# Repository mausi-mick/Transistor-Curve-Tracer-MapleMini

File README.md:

# Transistor-Curve-Tracer-MapleMini

This project based on the super project "Transistor Curve Tracer" from Peter Balch :
https://www.instructables.com/id/Transistor-Curve-Tracer/  

I ported the software from the 8-bit Arduino platform ( hardware: Arduino Pro Mini ) to 32 bit STM32duino (hw: MapleMini).

For me was the MapleMini the best choice: cheap, quick, enough program-space, more accessible port-pins as the Arduino Uno/Nano/... and more flexibility and accuracy :

more than 5 ADC's with 12-bit resolution, 2 SPI's/, more than 2 ISR-Pins (for the encoders) and USB-socket for programming and supply. 
Also the 3.3 V port-voltage was favourable for connections to the ILI9341-spi-tft-display/touch.

For more information about MapleMini look here: https://www.stm32duino.com/
or about this project:  https://www.stm32duino.com/viewtopic.php?t=4269

Therefore I had the possibility to integrate other features:

- integration of two rotary encoders (on isr) for a more comfortable changing of the parameters, a dual DAC (MCP4822) with the same 12-bit resolution as the ADC's on the MapleMini.
- possibility to save the parameters in the internal EEPROM
- possibility compare similar or complementary devices on the same screen
- changing x-scale for diodes/zeners (0,1,2,3,4,6,12,24V) (0: starts with 24V and search the optimal scale)
- changing y-sacle for diodes from 0...10mA  to 0...50mA
- changing y-scale for MosFETs/jFETs automatic depending on max. IDss from 50mA to 10mA or 50mA to 100mA
- changing x-scale for n-jFETs from 12V (default), 6V, 4V, 3V, 2V.

The schematic of the tracer is different from Peters version:

I use switches to connect the Emitter/Source/Cathode respectively Collector/Drain/Anode to +/- supply-voltage only while measuring - most time the DUT is only with the base connected, Emtter / Collector are isolated.
At first I tested it with a dual toggle switch, than with mechanical relais, than I changed to  PhotoMosRelais because of less space on the board and less supply-current( 40ma/5V -> 2-5mA/3.3V). So the MapleMini-ports can drive the PhotoMosRelais direct.

As amplifier to drive the Emitter/Source ... Collector/Drain I made another design.
Peter used a LM358 standard dual amplifier with emitter-followers, but I think it was difficult to make it stable and there was a big drop on the positive rail.
Therefore I searched and tested some other amplfiers with drive capacibility of more than 50mA, among others NE5532 , L2272 and TCA0372.
The TCA0372 was the best in relation to stability and to low drop on the supply (r-to-r) at 50mA.
I use only one amplifier of the TCA0372 with gain = +3 (default).
The output of the TCA0372 can manage more than 100mA, the negative supply-voltage I put down to about -3V, because the TCA0372 is not a real rail-to-rail-amplifier at this currents. The negative supply near -3V is generated with a charge-pump (from+3.3V).
With the U-DAC (MCP4822) I can generate 0...12V similar the version from Peter.
As amplifier for the base-current/gate-voltage I use a LT1013 dual amplifier, because it's a R to R and can work up to max. 44V.
The TCA0372 has a normal supply-voltage from 12.6V, changing to about 26V for measuring zeners with Vz > 12V and <= 24V. Therefore I have to change the gain of the TCA0372 to +6 (V-DAC-max  (=4.095V) * 6 >=24V).
For measuring nJFETS in the ohmic-region (< Vpinch) I can switch the x-scale at the display from 12V ... to 2V.
Between 2V and 4V the gain of the TCA0372 is switched from 3 to 2, the V-DAC MCP4822 works than from 0...2.047V with step = 0,5mV.  

The LT1013 has a positive supply-voltage from around 26V, a negative supply from -12v via a LM317L and ICL7662 charge-pump.
I need the negative supply for the gates from nJFET's and depletion-mode-nMOSFET's, the positive supply > 12V for the gates from 
p-JFET's (I think it exist only one depletion-mode-pMOSFET-chip!).

The gain of the opamp's of the LT1013 can be changed from +6 to -6 with two PhotoMosRelais, or better 
over the relais I can select the opamp with the gain +6 or -6.

For npn/pnp and MosFets the I-DAC here works from 0... 2.047 V to generate 0 ... + 12 V with gain = +6 or
with gain = -6  to generate 0 ... - 12 V gatevoltage for nJFET's,
for pJFET's the I-DAC works from about 2.048 ... 4.095 V to generate gatevoltage from +12 ... +24 V for
pJFET with gain +6.

The current is limited to max 50mA . only for JFET's/MOSFET's it can go in a second step up to about 100mA.

The software is developed with the ARDUINO IDE 1.8.4, STM32duino is about one year (2017) old, but I think the newest version would work to.

You have to load  Bootloader 2.0 (20k RAM, 120k Flash) in MapleMini.

The main components are:

- ILI9341 TFT-SPI-Display 2.8" with Touch ca 6.70 €
- MapleMini                                  3.60 €
- DACMCP4822                                 3.20 € 
- AQY212 6x                                  6.00 €
- LT1013                                     1.40 €
- TCA0372                                    1.10 €
- MT3608 3x                                  2.00 €
- Rotary Encoder 2x                          2.00 €
- nMOS switch    7x                          2.00 €    
- ICL7662 (-12V) + TSP490603(-5/-3.3V)       4.00 €
-                           SUM:            32.00 €
+ resistors, capacitors, diodes, test-sockets,                                          
+ pcb's, wire, zinn, sockets, battery, chassis ...     

The hardware is nearly finsihed, the software is growing !

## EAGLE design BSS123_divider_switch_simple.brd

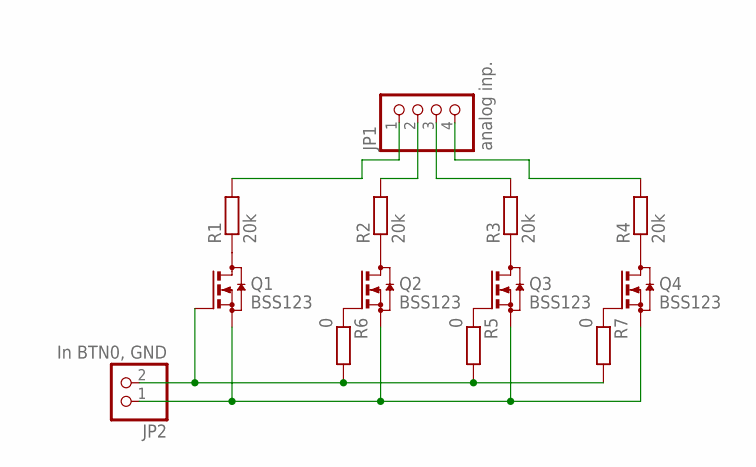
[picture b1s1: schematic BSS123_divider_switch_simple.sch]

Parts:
JP1: analog inp.; 1X04
JP2: In BTN0, GND; 1X02
Q1, Q2, Q3, Q4: BSS123; SOT23
R1, R2, R3, R4: 20k; R1206
R5, R6, R7: 0; R1206

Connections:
unnamed: Q1.3 (D), R1.1
unnamed: Q2.3 (D), R2.1
unnamed: Q3.3 (D), R3.1
unnamed: Q4.3 (D), R4.1
unnamed: Q4.1 (G), R7.1
unnamed: JP2.1, Q1.2 (S), Q2.2 (S), Q3.2 (S), Q4.2 (S)
unnamed: JP1.1, R1.2
unnamed: JP1.2, R2.2
unnamed: JP1.3, R3.2
unnamed: JP1.4, R4.2
unnamed: Q2.1 (G), R6.1
unnamed: Q3.1 (G), R5.1
unnamed: JP2.2, Q1.1 (G), R5.2, R6.2, R7.2

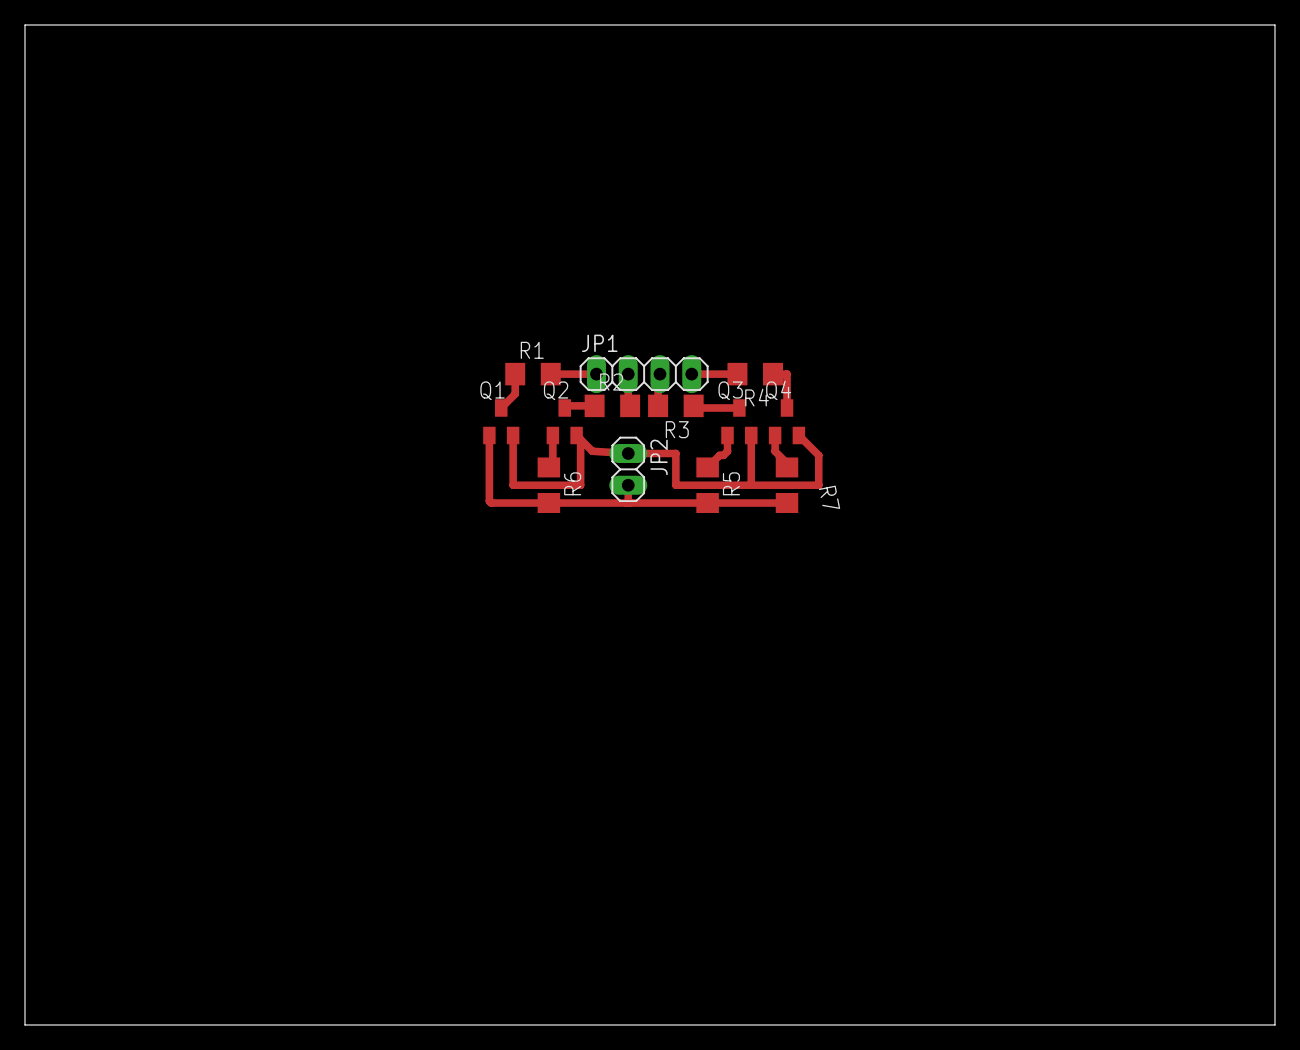
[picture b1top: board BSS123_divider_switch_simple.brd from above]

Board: 2 copper layers, 100.0 x 80.0 mm, 13 parts (0 on the bottom side), 13 nets.

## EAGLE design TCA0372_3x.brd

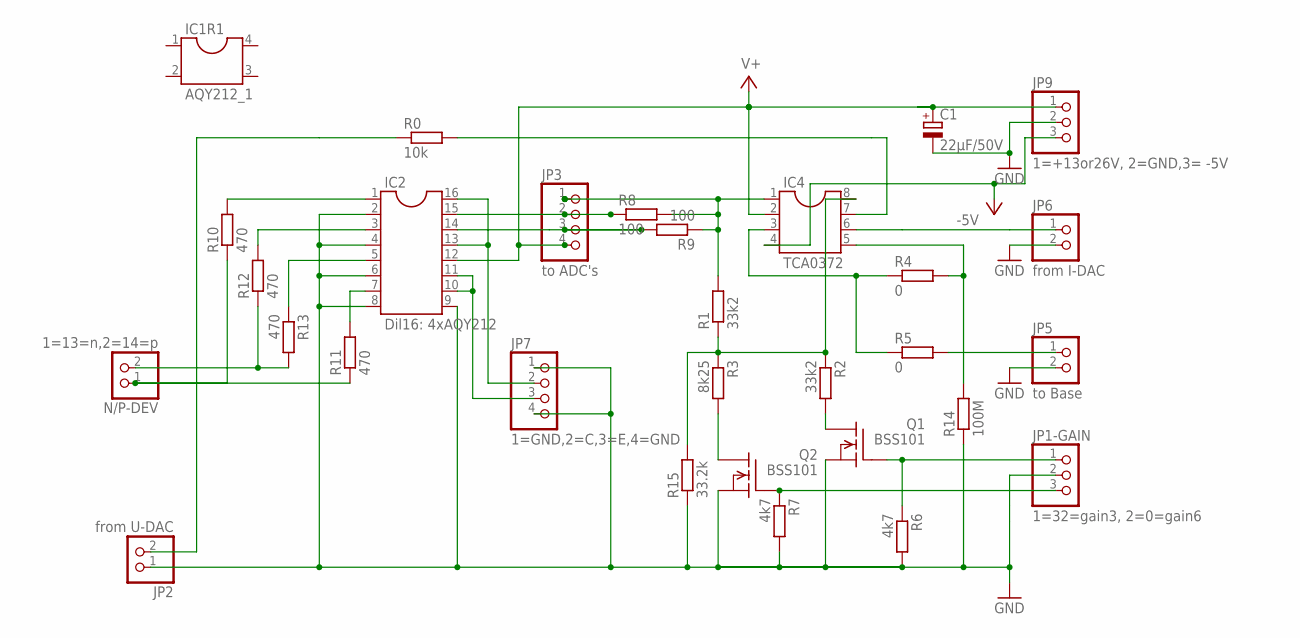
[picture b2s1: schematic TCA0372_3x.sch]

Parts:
C1: 22µF/50V; E5-10,5
IC1R1: AQY212_1; SOCKET-04
IC2: Dil16: 4xAQY212; SOCKET-16
IC4: TCA0372; SOCKET-08
JP1-GAIN: 1=32=gain3, 2=0=gain6; 1X03
JP2: from U-DAC; 1X02
JP3: to ADC's; 1X04
JP5: to Base; 1X02
JP6: from I-DAC; 1X02
JP7: 1=GND,2=C,3=E,4=GND; 1X04
JP9: 1=+13or26V, 2=GND,3= -5V; 1X03
N/P-DEV: 1=13=n,2=14=p; 1X02
Q1, Q2: BSS101; TO92
R0: 10k; 0207/7
R1, R2: 33k2; 0207/7
R3: 8k25; 0207/7
R4, R5: 0; 0207/7
R6, R7: 4k7; 0207/7
R8, R9: 100; 0207/7
R10, R11, R12, R13: 470; 0207/7
R14: 100M; 0207/7
R15: 33.2k; 0207/7

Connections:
-5V: IC4.4, JP9.3
GND: C1.-, IC2.2, IC2.4, IC2.6, IC2.8, IC2.9, JP1-GAIN.2, JP2.1, JP5.2, JP6.2, JP7.1, JP7.4, JP9.2, Q1.1 (S), Q2.1 (S), R6.2, R7.2, R14.1, R15.1
unnamed: IC4.5, R4.2, R14.2
unnamed: IC2.15, JP3.2, R8.1
unnamed: IC4.7, R0.2
unnamed: IC2.7, R11.2
unnamed: Q1.3 (D), R2.2
unnamed: Q2.3 (D), R3.2
unnamed: JP1-GAIN.1, Q1.2 (G), R6.1
unnamed: JP1-GAIN.3, Q2.2 (G), R7.1
unnamed: IC4.6, JP6.1
unnamed: IC2.3, R12.2
unnamed: IC2.13, IC2.16, JP7.2
unnamed: JP2.2, R0.1
unnamed: IC4.3, R4.1, R5.1
unnamed: IC2.5, R13.1
unnamed: N/P-DEV.2, R12.1, R13.2
unnamed: IC2.1, R10.2
unnamed: N/P-DEV.1, R10.1, R11.1
unnamed: JP5.1, R5.2
unnamed: IC4.1, JP3.1, R1.2, R8.2, R9.1
unnamed: IC4.8, R1.1, R2.1, R3.1, R15.2
unnamed: IC2.10, IC2.11, JP7.3
unnamed: IC2.14, JP3.3, R9.2
V+: C1.+, IC2.12, IC4.2, JP3.4, JP9.1

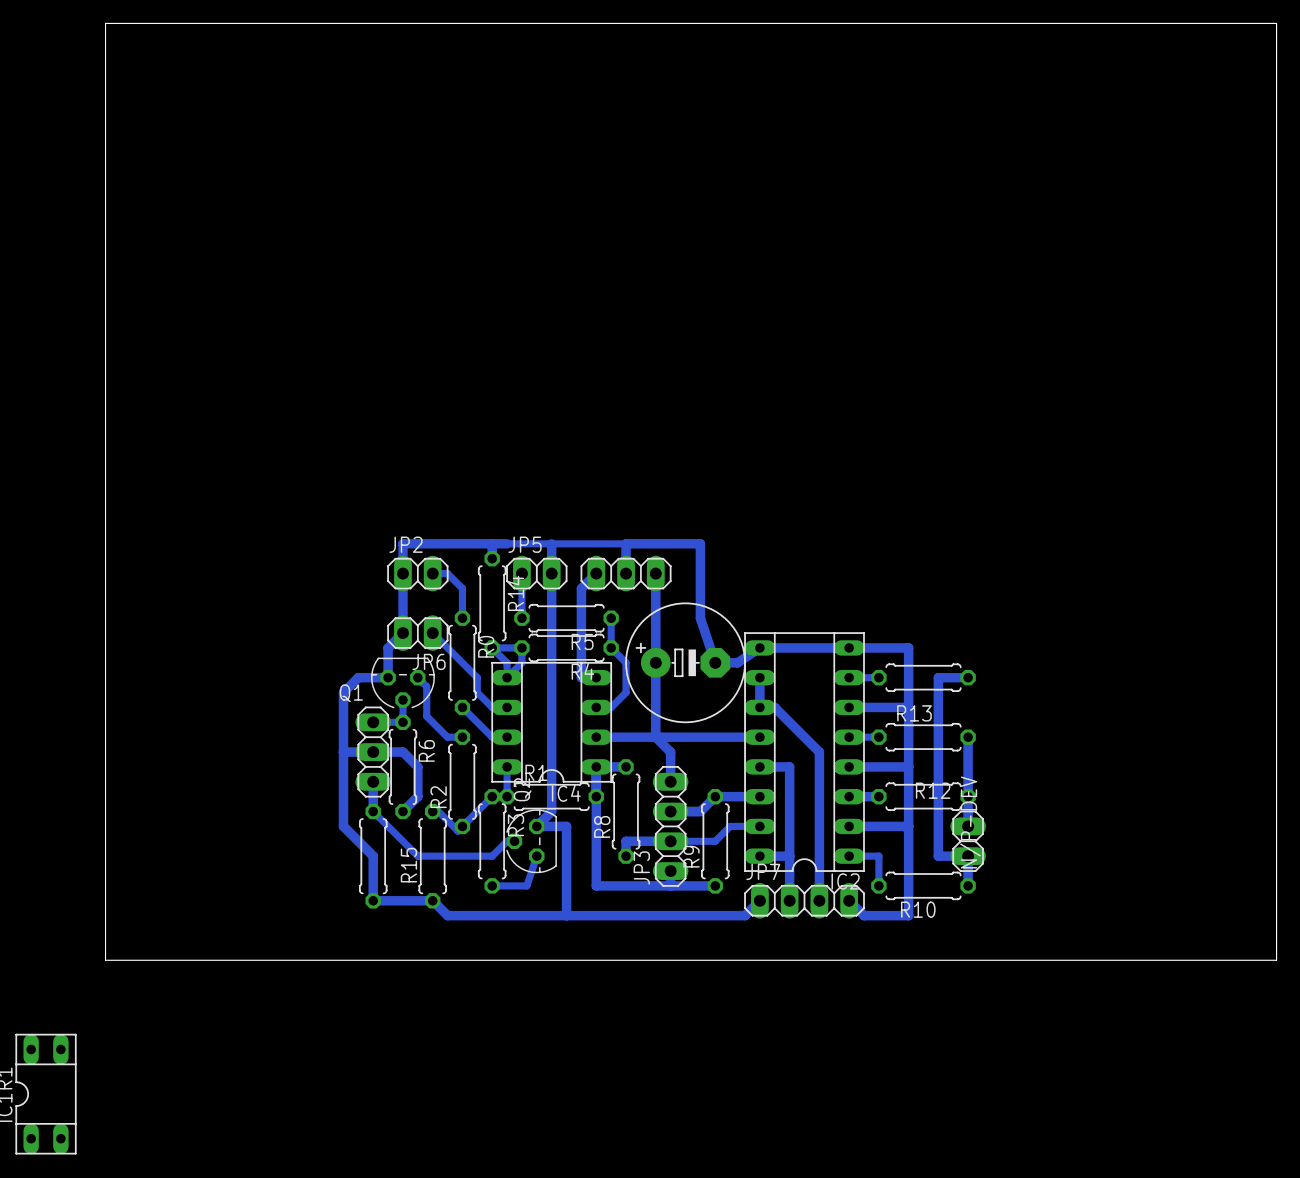
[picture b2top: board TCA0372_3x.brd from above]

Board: 2 copper layers, 100.0 x 80.0 mm, 30 parts (0 on the bottom side), 25 nets.

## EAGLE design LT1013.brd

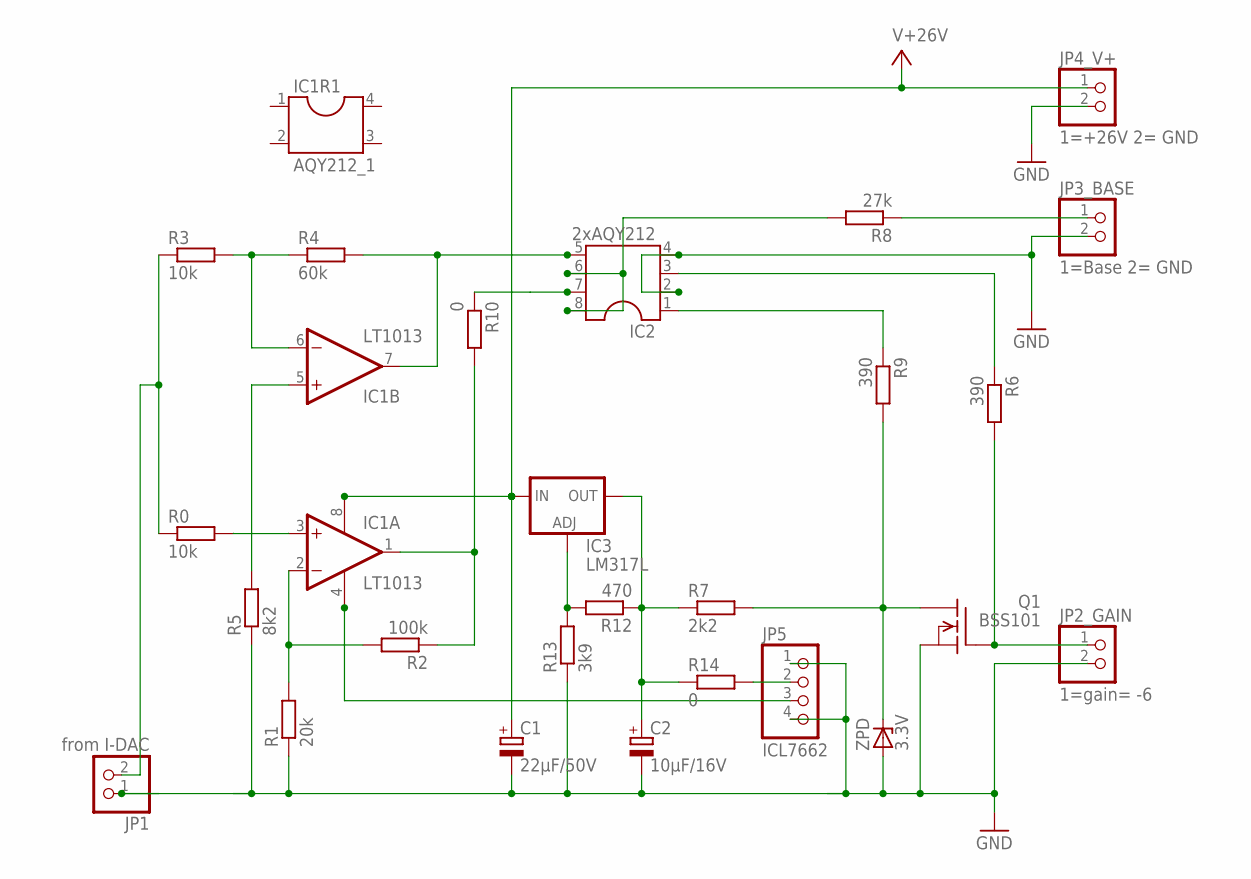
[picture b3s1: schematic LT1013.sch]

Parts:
C1: 22µF/50V; E5-10,5
C2: 10µF/16V; B45181B
IC1: LT1013; DIL08
IC1R1: AQY212_1; SOCKET-04
IC2: 2xAQY212; SOCKET-08
IC3: LM317L; 317L
JP1: from I-DAC; 1X02
JP2_GAIN: 1=gain= -6; 1X02
JP3_BASE: 1=Base 2= GND; 1X02
JP4_V+: 1=+26V 2= GND; 1X02
JP5: ICL7662; 1X04
Q1: BSS101; TO92
R0, R3: 10k; 0207/7
R1: 20k; 0207/7
R2: 100k; 0207/7
R4: 60k; 0207/7
R5: 8k2; 0207/7
R6, R9: 390; 0207/7
R7: 2k2; 0207/7
R8: 27k; 0207/7
R10, R14: 0; 0207/7
R12: 470; 0207/7
R13: 3k9; 0207/7
ZPD: 3.3V; ZDIO-7.5

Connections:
GND: C1.-, C2.-, IC2.2, IC2.4, JP1.1, JP2_GAIN.2, JP3_BASE.2, JP4_V+.2, JP5.1, JP5.4, Q1.1 (S), R1.1, R5.1, R13.1, ZPD.A
unnamed: IC1.6 (-IN), R3.2, R4.1
unnamed: IC1.2 (-IN), R1.2, R2.2
unnamed: IC1.1 (OUT), R2.1, R10.2
unnamed: IC1.3 (+IN), R0.2
unnamed: IC2.1, R9.1
unnamed: IC1.7 (OUT), IC2.5, R4.2
unnamed: Q1.3 (D), R7.2, R9.2, ZPD.C
unnamed: JP5.2, R14.2
unnamed: JP3_BASE.1, R8.1
unnamed: IC2.6, IC2.8, R8.2
unnamed: JP2_GAIN.1, Q1.2 (G), R6.2
unnamed: JP1.2, R0.1, R3.1
unnamed: IC1.5 (+IN), R5.2
unnamed: IC2.3, R6.1
unnamed: IC2.7, R10.1
unnamed: IC1.4 (V-), JP5.3
unnamed: IC3.1 (ADJ), R12.2, R13.2
unnamed: C2.+, IC3.2 (OUT), R7.1, R12.1, R14.1
V+: C1.+, IC1.8 (V+), IC3.3 (IN), JP4_V+.1

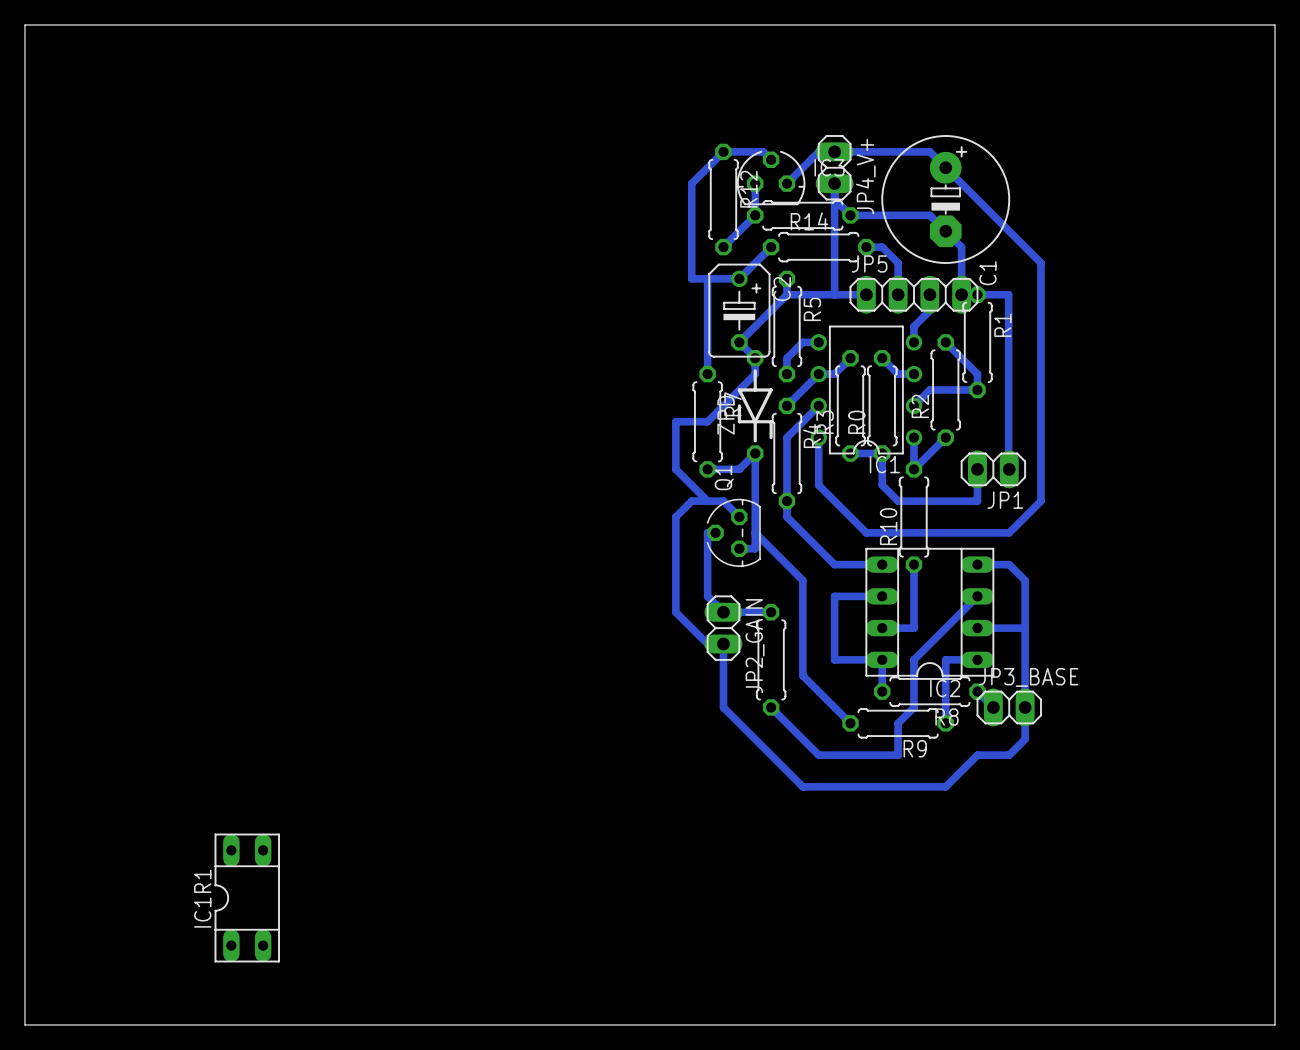
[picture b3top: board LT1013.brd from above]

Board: 2 copper layers, 100.0 x 80.0 mm, 27 parts (0 on the bottom side), 20 nets.

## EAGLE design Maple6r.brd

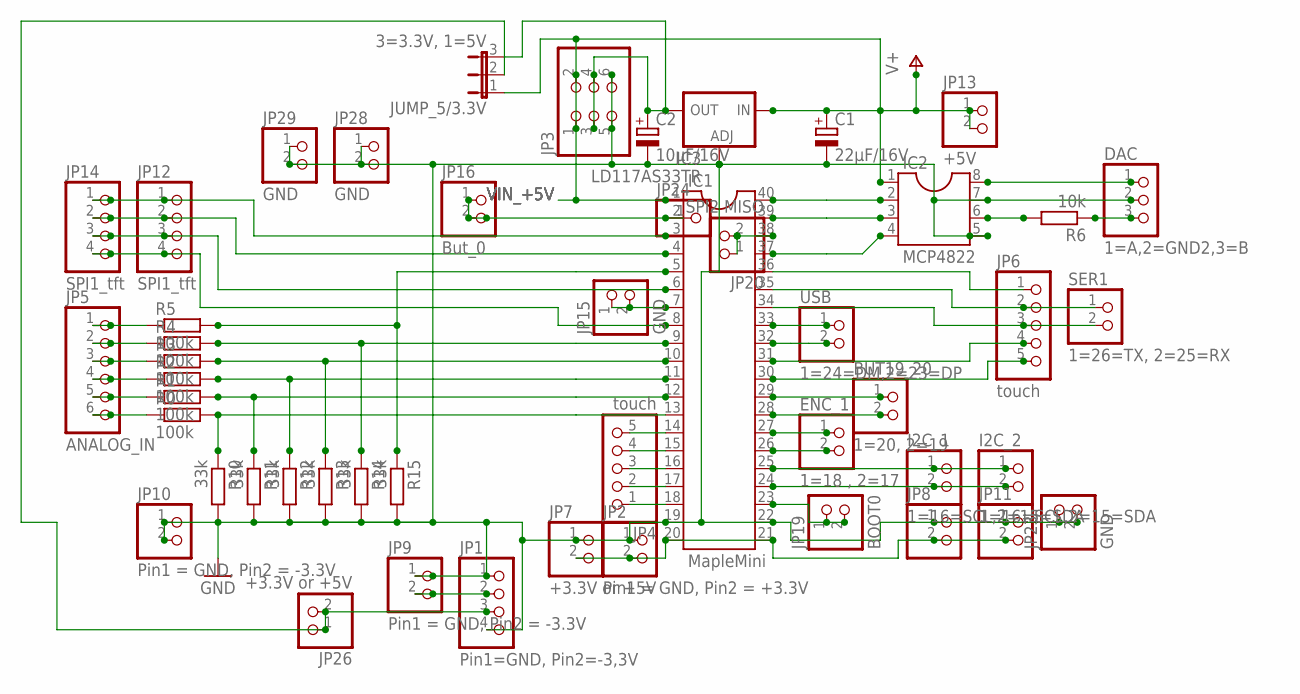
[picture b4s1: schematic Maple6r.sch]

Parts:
BUT19_20: 1=20, 2=19; 1X02
C1: 22µF/16V; E5-8,5
C2: 10µF/16V; E5-8,5
DAC: 1=A,2=GND2,3=B; 1X03
ENC_1: 1=18 , 2=17; 1X02
I2C_1, I2C_2: 1=16=SCL,2=15=SDA; 1X02
IC1: MapleMini; DIL40
IC2: MCP4822; SOCKET-08
IC3: LD117AS33TR; SOT223
JP1: Pin1=GND, Pin2=-3,3V; 1X04
JP2: Pin1 = GND, Pin2 = +3.3V; 1X02
JP3: PINHD-2X3; 2X03
JP4, JP6: touch; 1X05
JP5: ANALOG_IN; 1X06
JP7, JP26: +3.3V or +5V; 1X02
JP8, JP11: PINHD-1X2; 1X02
JP9, JP10: Pin1 = GND, Pin2 = -3.3V; 1X02
JP12, JP14: SPI1_tft; 1X04
JP13: +5V; 1X02
JP15, JP23, JP28, JP29: GND; 1X02
JP16: But_0; 1X02
JP19: BOOT0; 1X02
JP20: SPI2 MISO; 1X02
JP24: PINHD-1X1; 1X01
JUMP_5/3.3V: 3=3.3V, 1=5V; JP2
R0, R1, R2, R3, R4, R5: 100k; 0207/7
R6: 10k; 0207/7
R10, R11, R12, R13, R14, R15: 33k; 0207/7
SER1: 1=26=TX, 2=25=RX; 1X02
USB: 1=24=DM,2=23=DP; 1X02

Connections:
1_PB10: IC1.3, JP12.1, JP14.1
2_PB2: IC1.4, JP12.2, JP14.2
3_PB0: IC1.5, R5.2, R15.1
4_PA7: IC1.6, JP12.3, JP14.3
6_PA5: IC1.8, JP12.4, JP14.4
7_PA4: IC1.10, R3.2, R13.1
8_PA3: IC1.11, R2.2, R12.1
10_PA1: IC1.12, R1.2, R11.1
11_PA0: IC1.13, R0.2, R10.1
GND: C1.-, C2.-, DAC.2, IC1.19, IC1.22, IC2.5, IC2.7, IC3.1 (ADJ), JP1.1, JP1.4, JP2.1, JP3.5, JP3.6, JP7.1, JP8.1, JP9.1, JP10.1, JP10.2, JP11.1, JP23.1, JP23.2, JP28.1, JP28.2, JP29.1, JP29.2, R10.2, R11.2, R12.2, R13.2, R14.2, R15.2
unnamed: IC1.9, R4.2, R14.1
unnamed: JP5.1, R5.1
unnamed: JP5.2, R4.1
unnamed: JP5.3, R3.1
unnamed: JP5.4, R2.1
unnamed: JP5.5, R1.1
unnamed: JP5.6, R0.1
unnamed: IC1.30, JP6.5
unnamed: IC1.7, JP15.1, JP15.2
unnamed: IC1.32, USB.2
unnamed: IC1.2, JP16.1, JP16.2, JP24.1
unnamed: IC1.31, JP6.4
unnamed: JP1.2, JP9.2
unnamed: ENC_1.1, IC1.27
unnamed: JP1.3, JP26.1, JP26.2, JUMP_5/3.3V.2
unnamed: IC1.38, JP20.1, JP20.2
unnamed: IC1.33, USB.1
unnamed: IC1.36, JP6.1
unnamed: IC1.35, JP6.2, SER1.1
unnamed: IC2.6, R6.2
unnamed: IC1.40, IC2.2
unnamed: IC1.39, IC2.3
unnamed: IC1.14, JP4.5
unnamed: IC1.37, IC2.4
unnamed: IC1.15, JP4.4
unnamed: C2.+, IC3.4 (OUT), JP3.3, JP3.4, JUMP_5/3.3V.3
unnamed: IC1.34, JP6.3, SER1.2
unnamed: IC1.16, JP4.3
unnamed: IC1.17, JP4.2
unnamed: IC1.18, JP4.1
unnamed: BUT19_20.1, IC1.29
unnamed: BUT19_20.2, IC1.28
unnamed: ENC_1.2, IC1.26
unnamed: I2C_1.1, I2C_2.1, IC1.25
unnamed: I2C_1.2, I2C_2.2, IC1.24
unnamed: IC1.23, JP19.1, JP19.2
unnamed: IC1.20, IC1.21, JP2.2, JP7.2, JP8.2, JP11.2
unnamed: DAC.3, R6.1
unnamed: DAC.1, IC2.8
VIN_+5V: C1.+, IC1.1, IC2.1, IC3.3 (IN), JP3.1, JP3.2, JP13.1, JP13.2, JUMP_5/3.3V.1

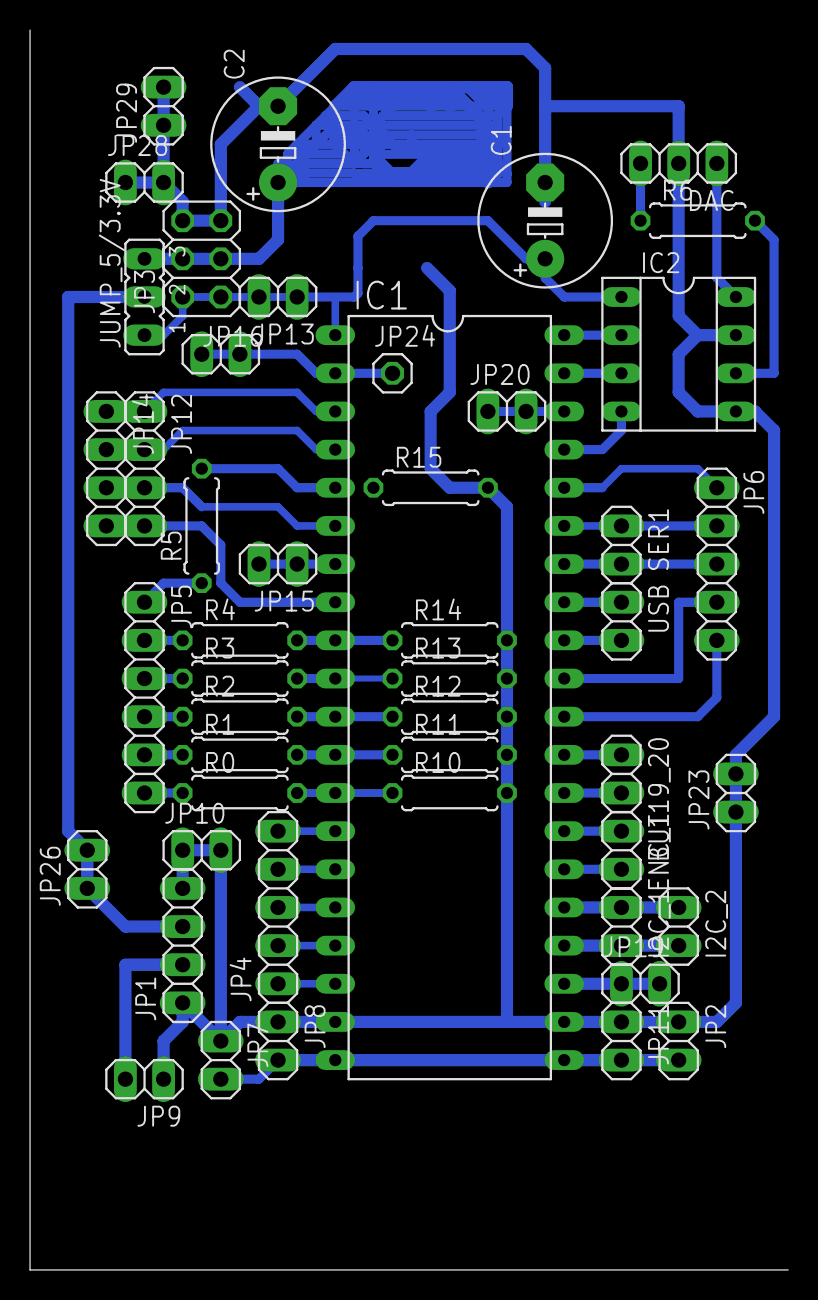
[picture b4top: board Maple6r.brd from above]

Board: 2 copper layers, 50.5 x 82.5 mm, 49 parts (1 on the bottom side), 50 nets.
